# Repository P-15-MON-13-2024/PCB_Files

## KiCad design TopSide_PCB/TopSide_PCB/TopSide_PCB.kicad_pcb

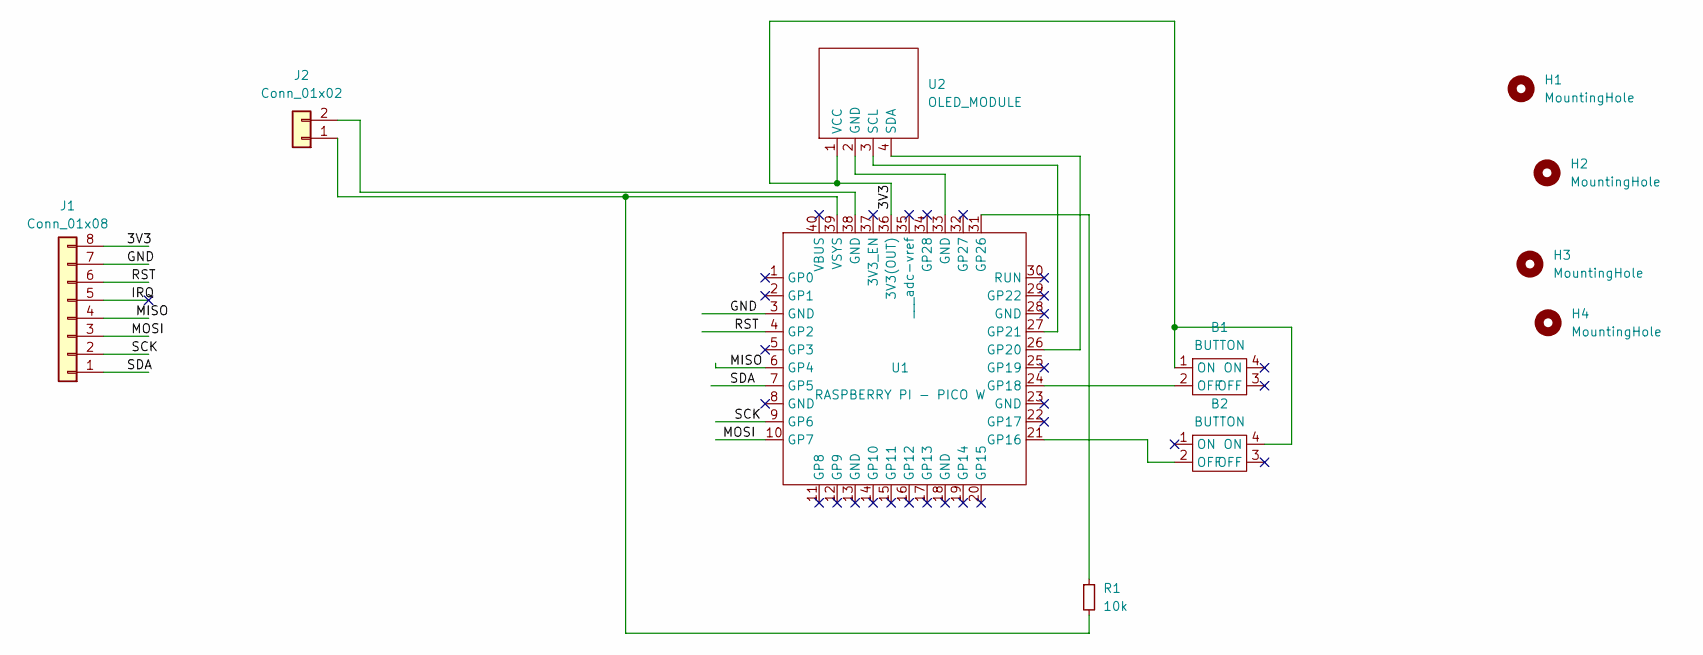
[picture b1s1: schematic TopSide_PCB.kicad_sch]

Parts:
B1, B2: BUTTON; Button
H1, H2, H3, H4: MountingHole; MountingHole_3mm
J1: Conn_01x08; PinHeader_1x08_P2.54mm_Horizontal
J2: Conn_01x02; PinHeader_1x02_P2.54mm_Horizontal
R1: 10k; R_0603_1608Metric
U1: RASPBERRY PI - PICO W; PICO_W
U2: OLED_MODULE; PinHeader_1x04_P2.54mm_Vertical

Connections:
/3V3: B1.1 (ON), B2.4 (ON), J1.8, U1.36 (3V3(OUT)), U2.1 (VCC)
/GND: J1.7, U1.3 (GND)
/IRQ: J1.5
/MISO: J1.4, U1.6 (GP4)
/MOSI: J1.3, U1.10 (GP7)
/RST: J1.6, U1.4 (GP2)
/SCK: J1.2, U1.9 (GP6)
/SDA: J1.1, U1.7 (GP5)
unnamed: J2.1, R1.2, U1.39 (VSYS)
unnamed: J2.2, U1.38 (GND)
unnamed: B2.2 (OFF), U1.21 (GP16)
unnamed: B1.2 (OFF), U1.24 (GP18)
unnamed: U1.26 (GP20), U2.4 (SDA)
unnamed: U1.27 (GP21), U2.3 (SCL)
unnamed: R1.1, U1.31 (GP26)
unnamed: U1.33 (GND), U2.2 (GND)

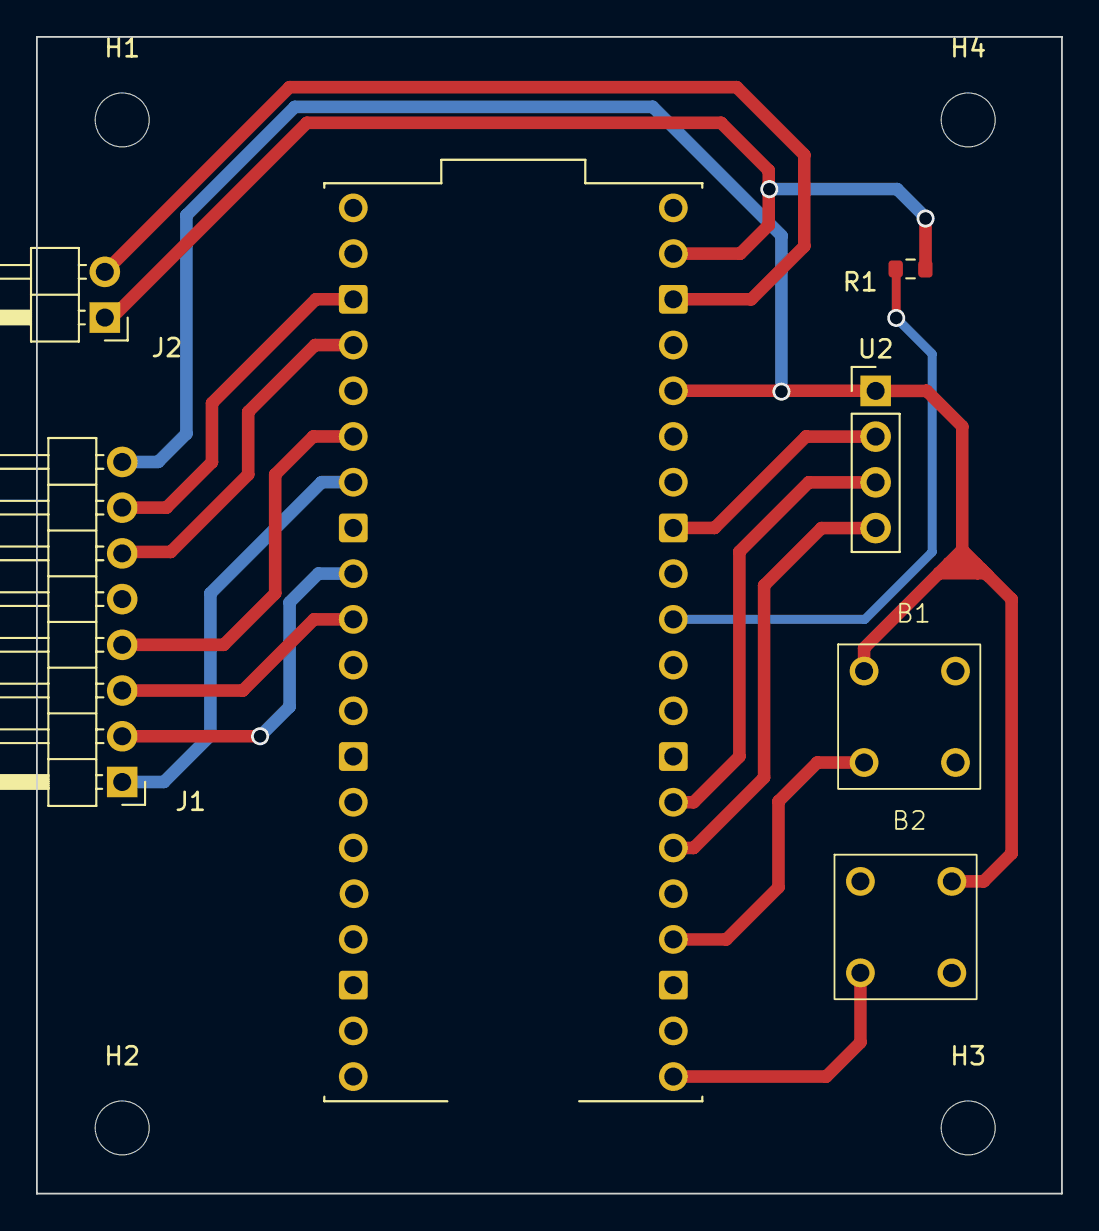
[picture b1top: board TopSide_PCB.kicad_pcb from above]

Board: 2 copper layers, 56.9 x 64.3 mm, 11 parts (0 on the bottom side), 15 nets.

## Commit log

2024-04-19 Added PCB files
